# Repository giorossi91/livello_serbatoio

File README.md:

# Tank level monitor

## Scope
This project realizes a simple device to monitor the water level in a tank.

## Architecture
The monitor is realized with an ATMEGA328P microcontroller to run the SW produced with Arduino IDE environment, an ultrasonic sensor to measure the level of the water and an LCD 16x2 characters to show the liters amount associated to the percentage of filling.

## Sofware
The SW has been developed with Arduino IDE and tested with CppUnit and a Qt GUI used to simulate the external environment.

## Phases of the project
### Phase 1 (Prototype)
The project was realized on a prototype board using the schematic in `schemi\schema_scheda.pdf`. The microcontroller was hosted in an Arduino UNO rev3 board.
The schematic was realized with Fritzing. The enclosure was hand-made and adapted from an existing one.

### Phase 2 (Finished)
The entire schematic was re-designed with Kicad and a PCB has been designed and produced. The enclosure has been designed with Freecad and 3D printed.

## Project Website
Go to [project website](https://giorossi91.github.io/livello_serbatoio)

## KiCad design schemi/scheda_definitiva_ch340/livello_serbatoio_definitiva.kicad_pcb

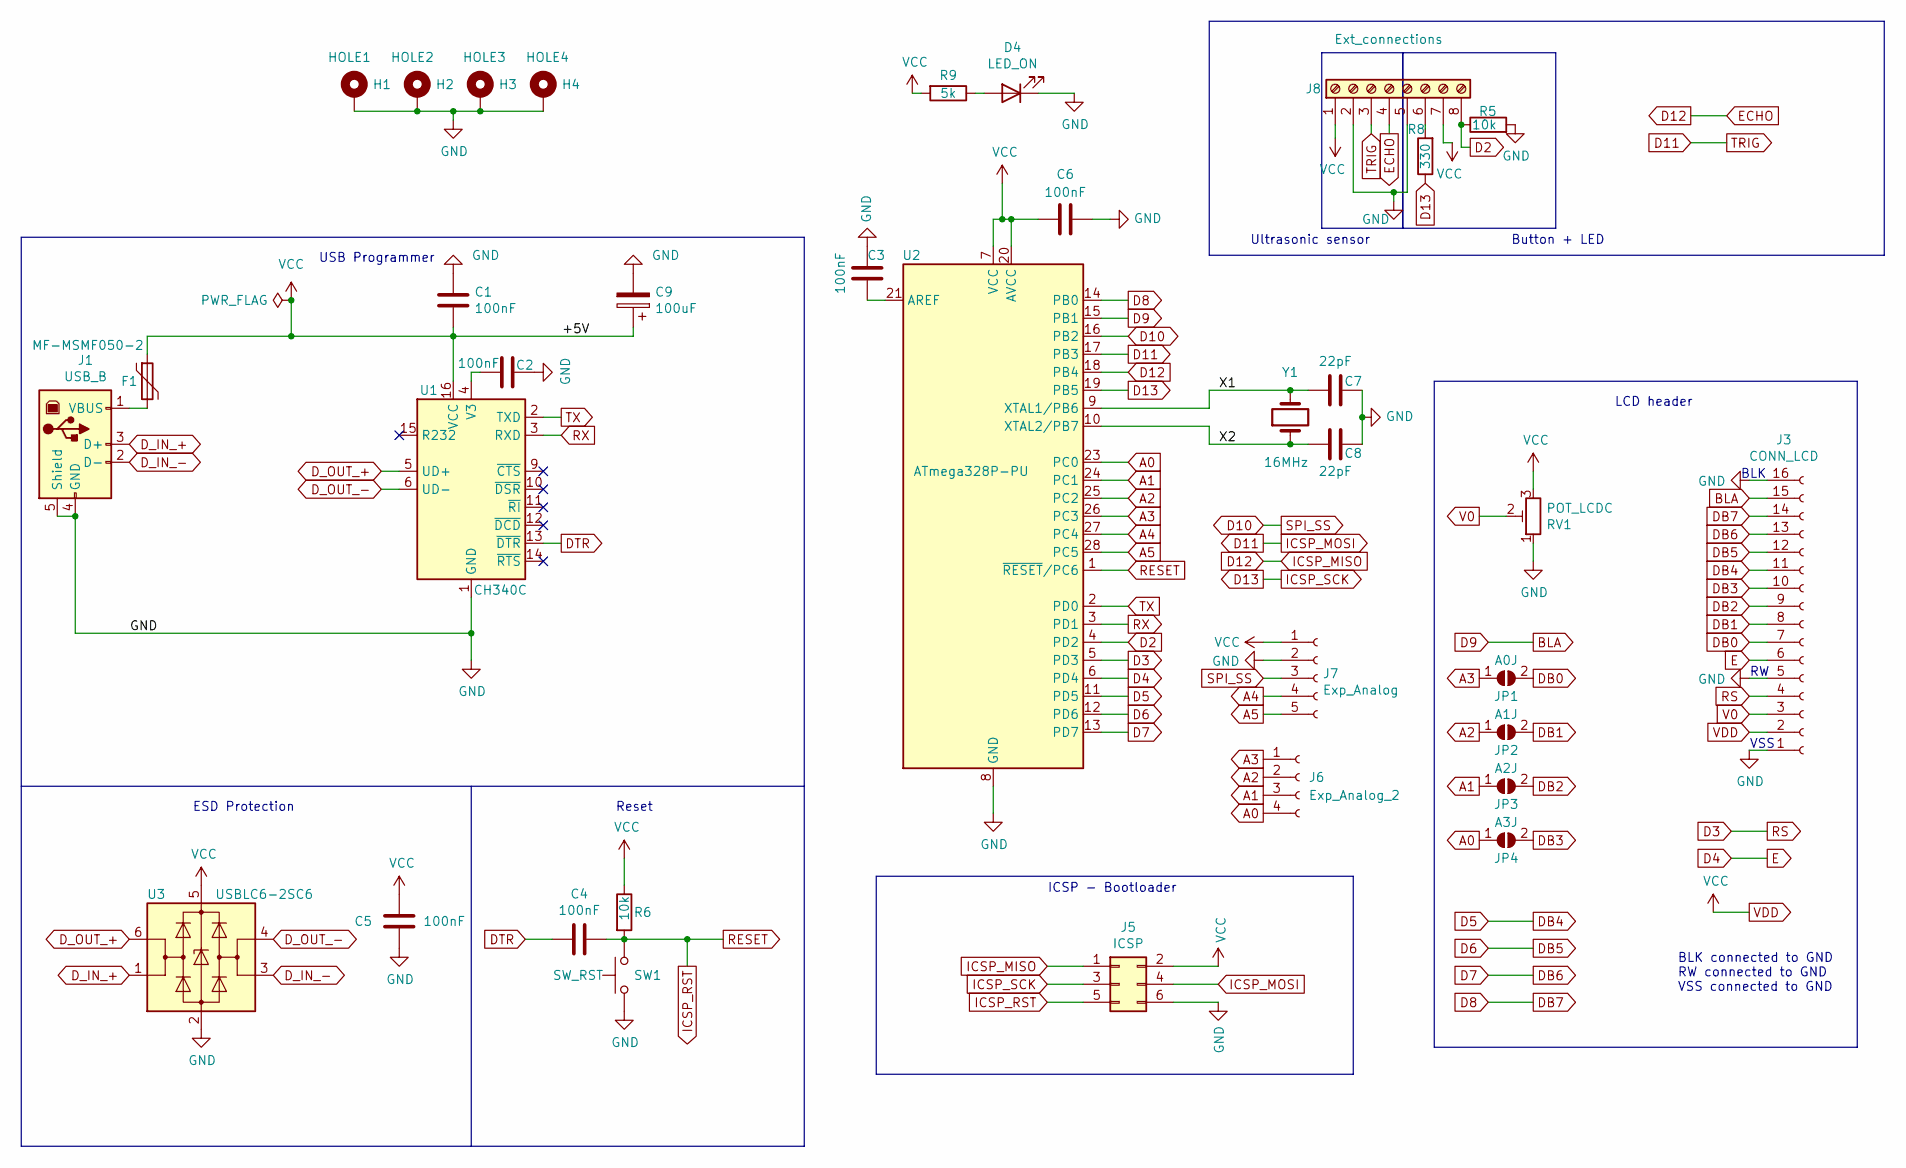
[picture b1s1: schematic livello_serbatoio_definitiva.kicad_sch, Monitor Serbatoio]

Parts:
C1, C2, C3, C4, C5, C6: 100nF; C_Disc_D5.0mm_W2.5mm_P2.50mm
C7, C8: 22pF; C_Disc_D5.0mm_W2.5mm_P2.50mm
C9: 100uF; CP_Radial_D5.0mm_P2.00mm
D4: LED_ON; LED_D5.0mm
F1: MF-MSMF050-2; MF-MSMF_1812_4532Metric_Pad1.30x3.40mm_HandSolder
H1: HOLE1; MountingHole_3mm_Pad_Via
H2: HOLE2; MountingHole_3mm_Pad_Via
H3: HOLE3; MountingHole_3mm_Pad_Via
H4: HOLE4; MountingHole_3mm_Pad_Via
J1: USB_B; USB_B_OST_USB-B1HSxx_Horizontal
J3: CONN_LCD; PinSocket_1x16_P2.54mm_Vertical
J5: ICSP; PinHeader_2x03_P2.54mm_Vertical
J6: Exp_Analog_2; PinSocket_1x04_P2.54mm_Vertical
J7: Exp_Analog; PinSocket_1x05_P2.54mm_Vertical
J8: Ext_connections; TerminalBlock_RND_205-00051_1x08_P5.00mm_Horizontal
JP1: A0J; SolderJumper-2_P1.3mm_Open_Pad1.0x1.5mm
JP2: A1J; SolderJumper-2_P1.3mm_Open_Pad1.0x1.5mm
JP3: A2J; SolderJumper-2_P1.3mm_Open_Pad1.0x1.5mm
JP4: A3J; SolderJumper-2_P1.3mm_Open_Pad1.0x1.5mm
R5, R6: 10k; R_Axial_DIN0309_L9.0mm_D3.2mm_P12.70mm_Horizontal
R8: 330; R_Axial_DIN0309_L9.0mm_D3.2mm_P12.70mm_Horizontal
R9: 5k; R_Axial_DIN0309_L9.0mm_D3.2mm_P12.70mm_Horizontal
RV1: POT_LCDC; Trimmer_ACP_470
SW1: SW_RST; SW_PUSH_6mm_H5mm
U1: CH340C; SOIC-16_3.9x9.9mm_P1.27mm
U2: ATmega328P-PU; DIP-28_W7.62mm
U3: USBLC6-2SC6; SOT-23-6_Handsoldering
Y1: 16MHz; Crystal_TH_AS16_5mm

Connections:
/X1: C7.2, U2.9 (XTAL1/PB6), Y1.2
/X2: C8.2, U2.10 (XTAL2/PB7), Y1.1
A0: J6.4, JP4.1 (A), U2.23 (PC0)
A1: J6.3, JP3.1 (A), U2.24 (PC1)
A2: J6.2, JP2.1 (A), U2.25 (PC2)
A3: J6.1, JP1.1 (A), U2.26 (PC3)
A4: J7.4, U2.27 (PC4)
A5: J7.5, U2.28 (PC5)
BLA: J3.15, U2.15 (PB1)
D2: J8.8, R5.1, U2.4 (PD2)
D3: J3.4, U2.5 (PD3)
D4: J3.6, U2.6 (PD4)
D5: J3.11, U2.11 (PD5)
D6: J3.12, U2.12 (PD6)
D7: J3.13, U2.13 (PD7)
D8: J3.14, U2.14 (PB0)
D10: J7.3, U2.16 (PB2)
D11: J5.4, J8.3, U2.17 (PB3)
D12: J5.1, J8.4, U2.18 (PB4)
D13: J5.3, R8.1, U2.19 (PB5)
DB0: J3.7, JP1.2 (B)
DB1: J3.8, JP2.2 (B)
DB2: J3.9, JP3.2 (B)
DB3: J3.10, JP4.2 (B)
DTR: C4.2, U1.13 (~DTR)
D_IN_+: J1.3 (D+), U3.1 (I/O1)
D_IN_-: J1.2 (D-), U3.3 (I/O2)
D_OUT_+: U1.5 (UD+), U3.6 (I/O1)
D_OUT_-: U1.6 (UD-), U3.4 (I/O2)
GND: C1.1, C2.2, C3.2, C5.1, C6.2, C7.1, C8.1, C9.2, D4.1 (K), H1.1, H2.1, H3.1, H4.1, J1.4 (GND), J1.5 (Shield), J3.1, J3.5, J3.16, J5.6, J7.2, J8.2, J8.5, R5.2, RV1.1, SW1.1, U1.1 (GND), U2.8 (GND), U2.22 (GND), U3.2 (GND)
ICSP_RST: C4.1, J5.5, R6.2, SW1.2, U2.1 (~RESET/PC6)
unnamed: D4.2 (A), R9.1
unnamed: F1.2, J1.1 (VBUS)
unnamed: J8.6, R8.2
unnamed: C2.1, U1.4 (V3)
unnamed: C3.1, U2.21 (AREF)
RX: U1.3 (RXD), U2.3 (PD1)
TX: U1.2 (TXD), U2.2 (PD0)
V0: J3.3, RV1.2
VDD: C1.2, C5.2, C6.1, C9.1, F1.1, J3.2, J5.2, J7.1, J8.1, J8.7, R6.1, R9.2, RV1.3, U1.16 (VCC), U2.7 (VCC), U2.20 (AVCC), U3.5 (VBUS)

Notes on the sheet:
ESD Protection
BLK
Reset
USB Programmer
Ultrasonic sensor
BLK connected to GND RW connected to GND VSS connected to GND
VSS
Button + LED
ICSP - Bootloader
LCD header

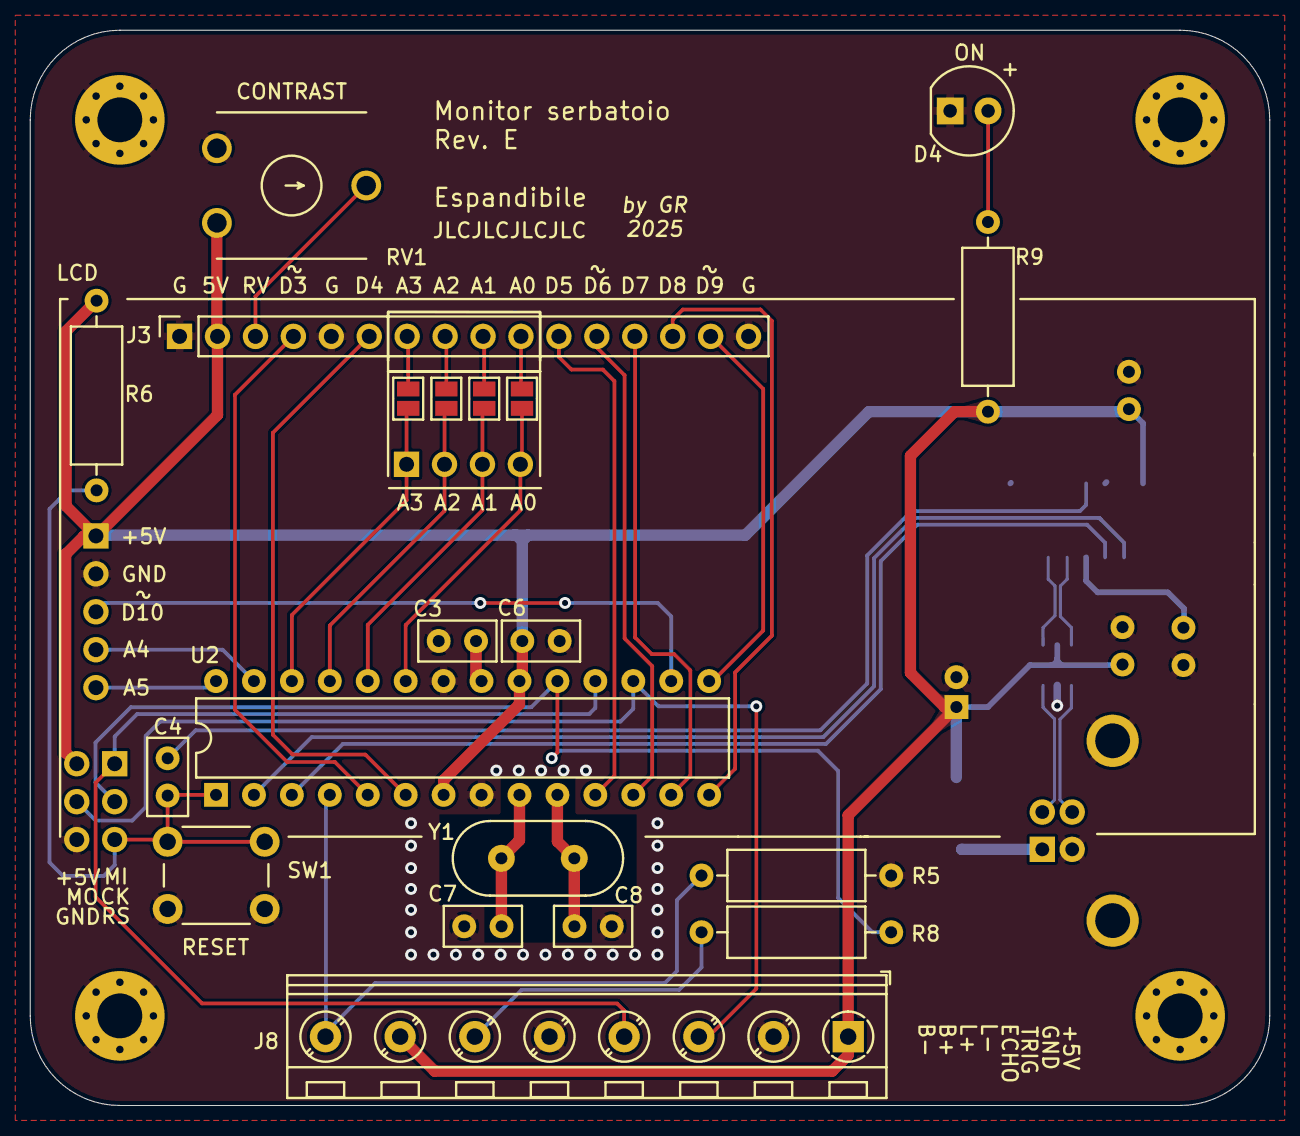
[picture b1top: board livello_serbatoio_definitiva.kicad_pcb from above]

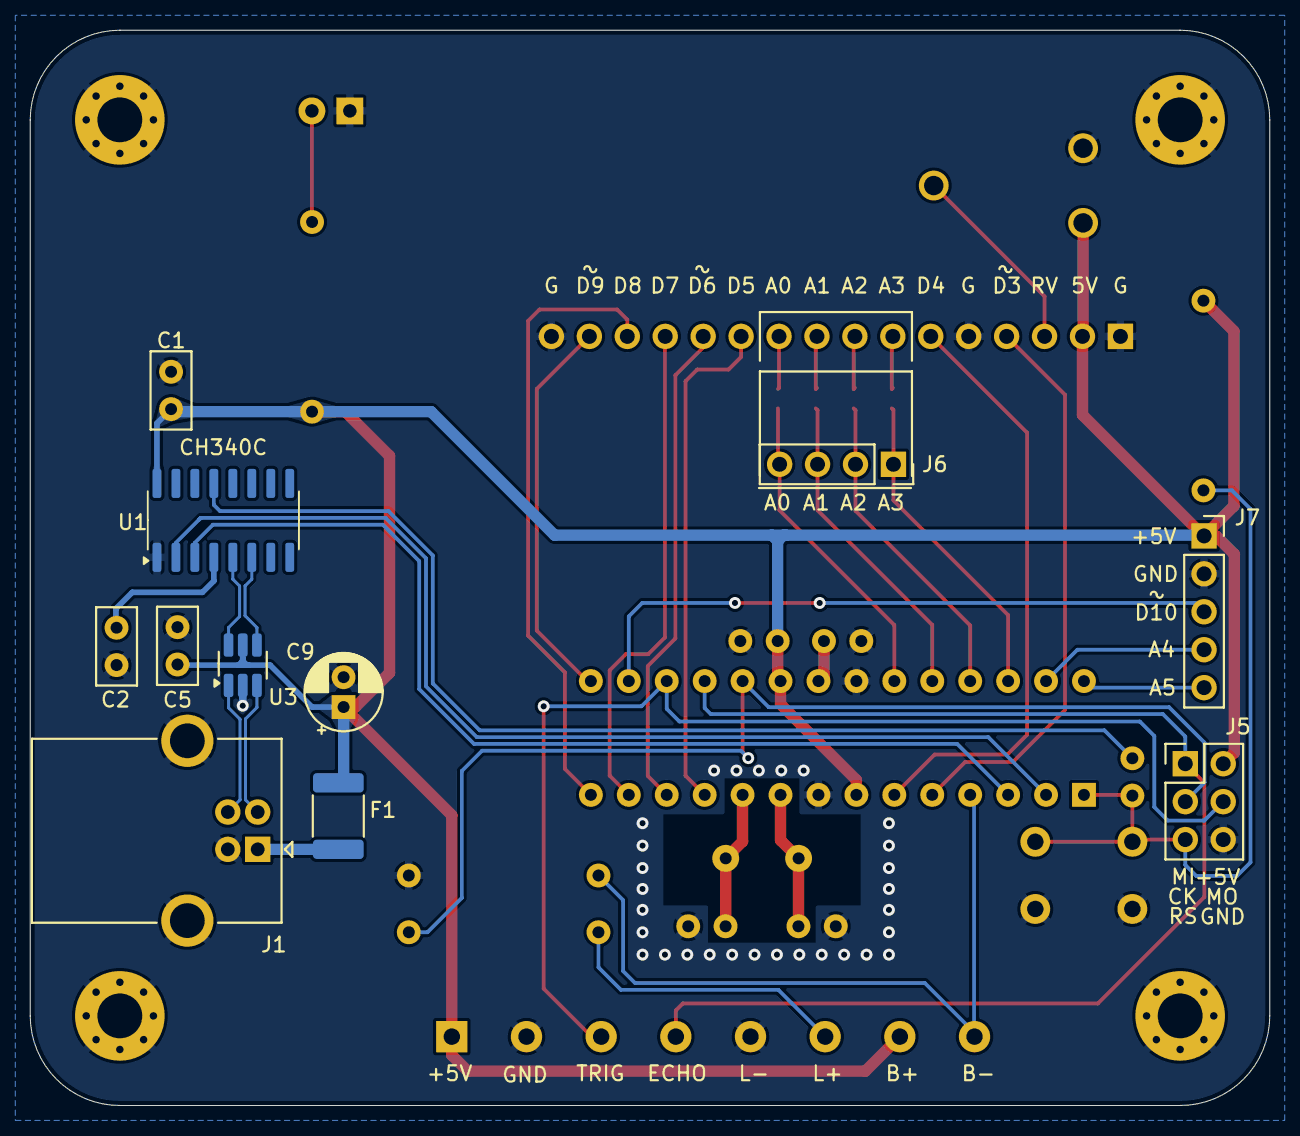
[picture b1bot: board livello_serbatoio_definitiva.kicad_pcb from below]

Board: 2 copper layers, 83.0 x 72.0 mm, 35 parts (11 on the bottom side), 40 nets.

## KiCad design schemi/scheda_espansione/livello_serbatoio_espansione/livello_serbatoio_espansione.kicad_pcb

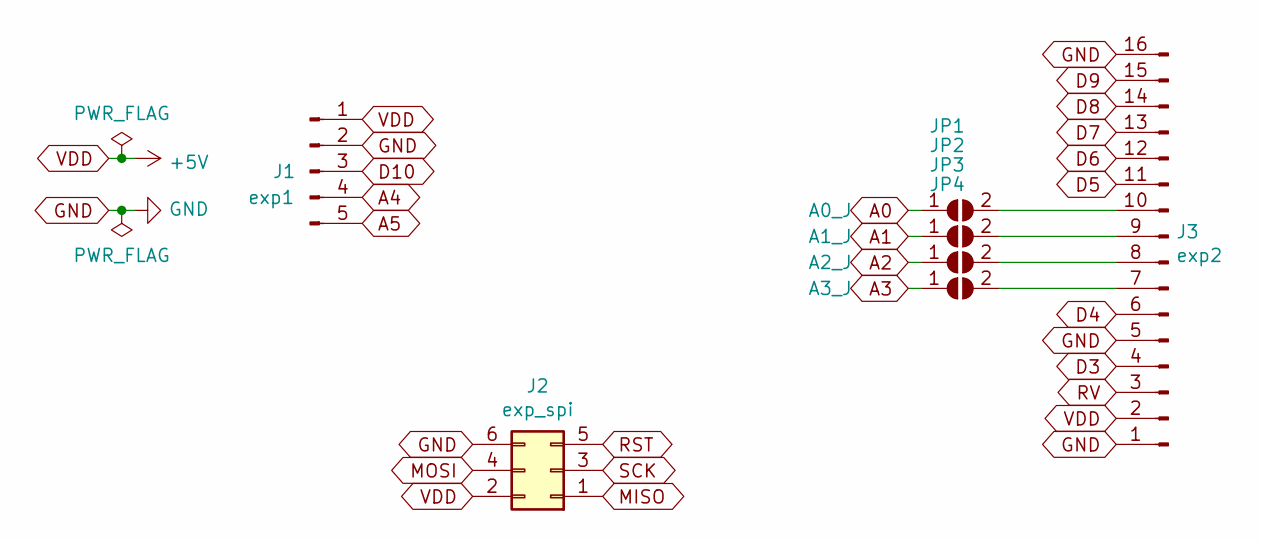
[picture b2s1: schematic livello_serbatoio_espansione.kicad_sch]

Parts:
J1: exp1; PinHeader_1x05_P2.54mm_Vertical
J2: exp_spi; PinSocket_2x03_P2.54mm_Vertical
J3: exp2; PinHeader_1x16_P2.54mm_Vertical
JP1: A0_J; SolderJumper-2_P1.3mm_Open_Pad1.0x1.5mm
JP2: A1_J; SolderJumper-2_P1.3mm_Open_Pad1.0x1.5mm
JP3: A2_J; SolderJumper-2_P1.3mm_Open_Pad1.0x1.5mm
JP4: A3_J; SolderJumper-2_P1.3mm_Open_Pad1.0x1.5mm

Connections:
A0: JP1.1 (A); also elsewhere on the board
A1: JP2.1 (A); also elsewhere on the board
A2: JP3.1 (A); also elsewhere on the board
A3: JP4.1 (A); also elsewhere on the board
A4: J1.4
A5: J1.5
D3: J3.4
D4: J3.6
D5: J3.11
D6: J3.12
D7: J3.13
D8: J3.14
D9: J3.15
D10: J1.3
GND: J1.2, J2.6, J3.1, J3.5, J3.16
MISO: J2.1
MOSI: J2.4
unnamed: J3.7, JP4.2 (B)
unnamed: J3.8, JP3.2 (B)
unnamed: J3.9, JP2.2 (B)
unnamed: J3.10, JP1.2 (B)
RST: J2.5
RV: J3.3
SCK: J2.3
VDD: J1.1, J2.2, J3.2

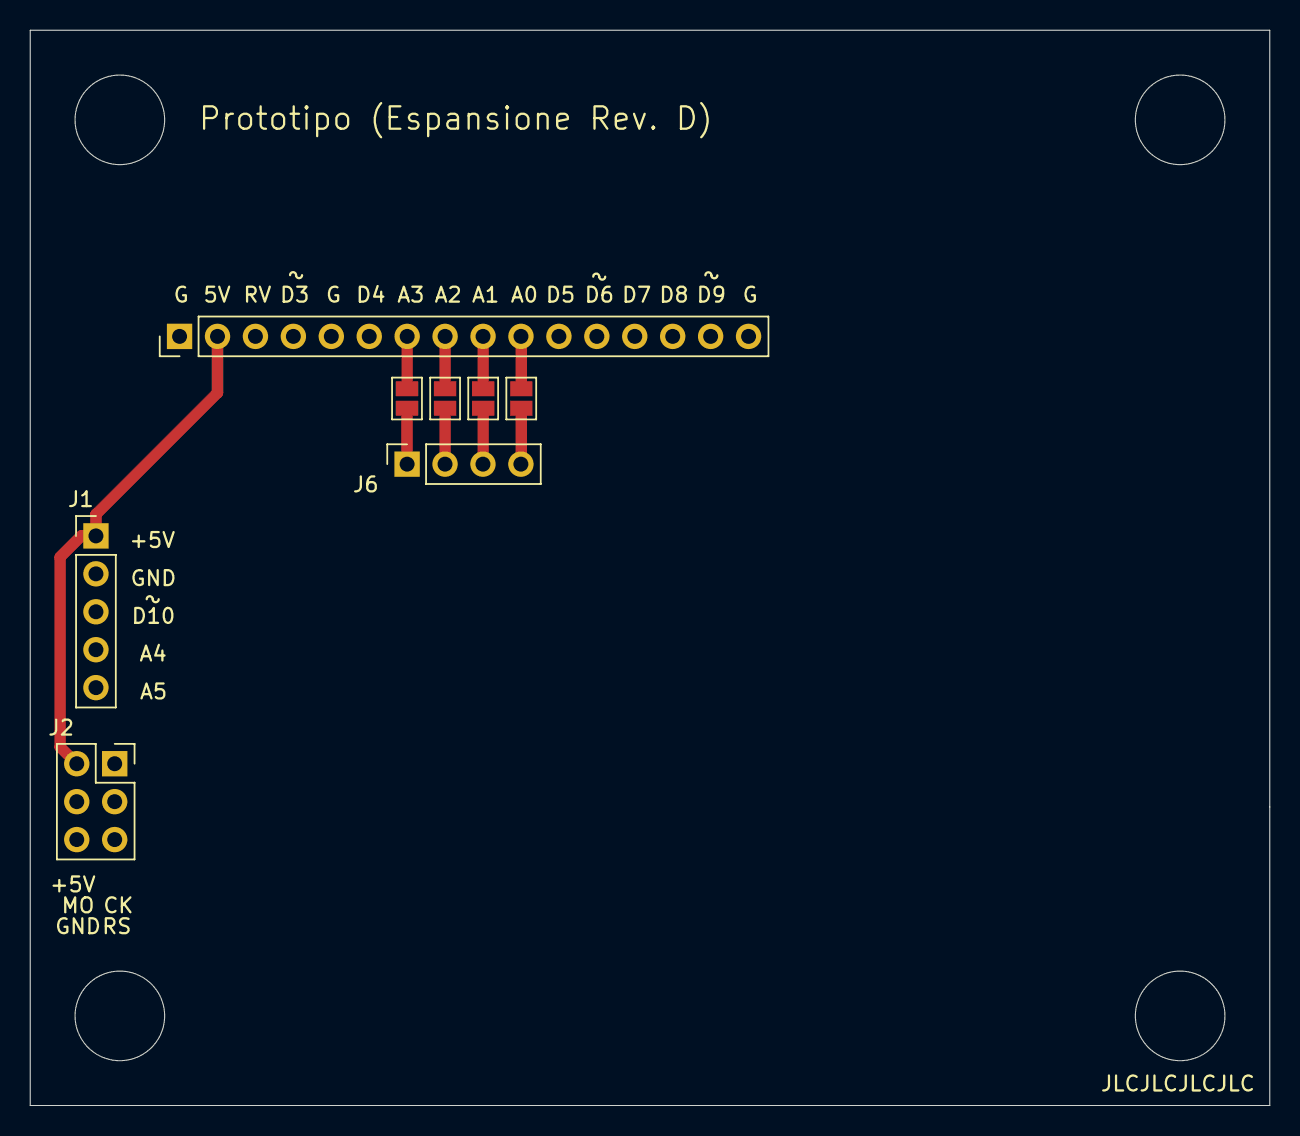
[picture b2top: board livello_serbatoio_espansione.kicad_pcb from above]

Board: 2 copper layers, 83.0 x 72.0 mm, 8 parts (0 on the bottom side), 10 nets.

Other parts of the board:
J6: Exp_Analog_2; PinSocket_1x04_P2.54mm_Vertical

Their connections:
A0: J6.4; also elsewhere on the board
A1: J6.3; also elsewhere on the board
A2: J6.2; also elsewhere on the board
A3: J6.1; also elsewhere on the board

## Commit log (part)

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2017-08-22 aggiunto script calcolo livello serbatoio
2017-08-29 aggiornato sketch - aggiunta distanza sensore da livello massimo - migliorata gestione timer lcd on e intervallo di misura - tradotti nomi variabili in inglese - calcolo capienza serbatoio corretto -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
2017-09-02 modifica layout lcd - modalità release + aggiunto schema pcb (bozza da completare)
2017-09-03 aggiornamento lcd
2017-09-09 aggiornato pinout
2017-12-26 fix misura litri
2017-12-26 implementato smoothing letture distanza
2017-12-26 introdotto median filter per i dati della distanza e aggiornato sketch
2018-01-27 aggiunto messaggio di boot + pdf schema
2018-01-27 modificata finestra lettura MedianFilter
2018-08-07 Taratura sensore + bug fixing - corretto rendering litri - corretti commenti - aumentato tempo campionamento - introdotto arrotondamento distanza a intero più vicino (migliore stabilità misure, preci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
2018-08-10 corretto controllo overflow distanza + introdotto check riempimento serbatoio con indicatore sul display (freccia custom)
2018-08-13 rimosso controllo riempimento (non utile) + ripristinato sleep a 1.5s per led
2018-08-18 rimosso PULL_UP a input lcd + cambiato carattere barra progresso
2018-11-10 introdotto controllo errore per funzione pulseIn
2018-11-10 aggiunto schematico scheda d'interfaccia
2018-12-23 Aggiunta compensazione errore del nuovo sensore
2019-08-08 Inserita doppia configurazione per vecchio sensore e nuovo waterproof - Calibrazione distanza
2019-08-11 Aggiornato sketch - Refactory codice - Risoluzione bug (refresh lcd, boot lungo, size variabili) - Aggiunta documentazione - Uniti file in un unico sketch
2019-08-16 bug fix + funzione autotest
2019-08-17 aggiunto gitignore
2019-08-17 Aggiunta classe per controllo statistiche [in implementazione]
2019-08-17 aggiunto print versione
2019-08-17 classe calcolo statistiche consumo
2019-08-20 aggiunta print stats su LCD (da testare)
2019-08-21 Completato display su LCD delle statistiche
2019-08-21 [da testare] fix statistiche consumo
2019-08-22 [da testare] fix soglia di riempimento in updateConsumption
2020-06-13 Riorganizzazione repository. Rimossa cartella MediaFilter in seguito ad integrazione in un file unico. Aggiunta cartella schemi che include tutti gli schematici realizzati in formato fritzing e pdf.
2020-06-13 Aggiunta base per unit testing con cppunit
2020-06-20 creata test harness per LCD e Serial e stub
2020-06-21 Aggiunto progetto Eclipse per supporto coverage
2020-06-28 Unit test e coverage - Aggiunti unit test per compute_liters, compute_percentage, turn_on_lcd_light, turn_off_lcd_light, measure_level, control_led, sanitize_data - Aggiunto rapporto coverage creato 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
2020-06-29 aggiunti nuovi test per LCD - vari fix sullo sketch - aggiornata coverage - aggiornato makefile
2020-08-02 nuovi test + schematico - bozza schematico per scheda definitiva (realizzato con KiCAD) - implementati nuovi test per MedianFilter - bozza test per StatisticheConsumo - piccole revisioni a sketch (ri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
2020-08-03 aggiornati unit test - nuovi test per StatisticheConsumo - fix su updateTime in StatisticheConsumo
2020-08-05 nuovi unit test + simulatore - aggiunti test per StatisticheConsumo - aggiunto simulatore Qt per testing e debugging senza scheda
2020-08-08 aggiunto grafico D/IO a simulatore
2020-08-09 migliorata gestione serie ed introdotto monitoraggio segnali
2020-08-13 nuovi test per funzione loop + modifiche a sketch - inizializzazione oggetti con metodo begin e initialize - fix stampa errore e recovery in seguito ad errore sensore
2020-08-14 test unitario loop completo
2020-08-17 fix a schema definitivo e assegnate footprint
2020-08-18 caricamento prima bozza PCB + piccoli fix a footprint
2020-08-19 modifiche a scheda definitiva - aggiunto footprint LCD di riferimento - modificato schematico per aggiungere connettore ICSP e fori di montaggio a massa - ricollocati connettori - da rivedere colloca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
2020-08-20 spostato UC in PCB per conflitto con LCD + aggiunto modello 3d Cristallo
2020-08-21 riposizionati connettori + auto-routing eseguito con freerouting
2020-08-22 Revisioni a PCB - aggiunta versione a PCB - revisione piste - generato piano di massa - aggiunto gerber
2020-08-22 prima bozza box da completare
2020-08-29 modello 3d completo - lcd - box
2020-10-11 fix alimentazioni + introduzione coppia differenziale per USB - da rivedere piste USB per match lunghezza/skew/impedenza
2020-10-18 spostati componenti e fatto nuovo sbroglio
2020-10-24 rivisto routing di alcune piste
2020-10-24 modifica traccia usb + rigenerato gerber
2020-10-25 modificato gerber / disegno 3D box / nuove immagini render aggiunte
2020-11-07 nuovo routing + BOM + aggiornamento lista componenti
2020-11-08 fix a scheda - corrette footprint (adeguate a componenti in possesso) - nuovo routing e layout scheda - aggiunto logo - aggiornato gerber
2020-11-14 aggiunta protezione ESD - nuovo routing usb - nuove immagini pcb
2020-11-15 allineamento modello 3d + fix minori pcb - aggiornato modello box - aggiunto logo a box - nuovi modelli 3d fusibile e trimmer - aggiornato sch per fusibile - aggiornato pcb - nuove immagini + doc pro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
2020-11-15 aggiornato gerber PCB
2020-11-21 revisione routing pcb
2020-11-21 esportati pin per espandibilità
2020-11-22 revisioni minime a pcb
2020-11-23 fix footprint trimmer - aggiornato pcb
2020-11-28 aggiornamento PCB - ridefinite filled zone - stondati bordi - cambiato connettore per espansione - rimosse via per GND
2020-11-29 piccole revisioni PCB - spostate alcune piste per maggiore copertura filled zone - rivisti alcuni parametri per manufacturing (dimensione scritte, S/N) - rimosse alcune vie e piste per piano GND inut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
2020-11-30 revisionata connessione DTR logica reset - revisionato wiring DTR - aggiornato PCB - ricreato gerber
2020-12-01 revisione piste circuito reset - spostata pista DTR - spostato pulsante - aggiornato piano di massa - rimossa una via su DTR
2020-12-04 aggiunto ulteriore connettore per espansioni - riviste piste - rivisti piani di massa
2020-12-05 revisione pcb - fix misure lcd - spostate alcune piste
2020-12-06 aumentate dimensioni track +5V - rivisto layout di alcune piste - aggiunti commenti su layout
2020-12-08 spostato LCD e rifatto modello box - LCD centrato su LCD - revisione layout - nuovo modello box (box + coperchio + pulsante + assembly scheda e lcd) - aggiornate immagini prototipo - creati file stl 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
2020-12-12 creato modello 3d box ad incastro
2020-12-20 fix mesh box
2020-12-20 aggiunta tolleranza ad incastro
2020-12-22 piccoli fix a PCB
2020-12-24 Creata prima bozza README
2020-12-27 aggiunte piazzole CTS/RTS + aggiunte etichette a pin digitali - rivisto gerber - rivista footprint oscillatore
2020-12-28 fix serigrafie PCB - generato gerber - caricamento test seriale
2020-12-30 caricamento prototipo espansione - schema elettrico + pcb - assemblaggio 3d con scheda di espansione
2021-02-13 modifica per seriale - aggiunto elettrolitico per alimentazione - fix test seriale
2021-03-06 aggiunta ferrite a scheda rev. B
2021-05-23 disconnesso pin reset di ft232
2021-06-27 Rimosso interrupt a pressione pulsante ed introdotto tempo di pressione corto - Aggiornato simulatore - Aggiornati unit test
2021-08-06 modificata gestione pulsante e aggiunta modalità maintenance
2021-08-07 Refactory - funzione menu con un tasto - traduzione commenti in inglese - rinomina variabili per uniformità
2021-08-08 Refactory - completata documentazione codice - aggiunta opzione menu per visualizzare i parametri dei serbatoi
2021-08-09 fix warning compilatore
2021-08-10 piccoli fix (commenti, formattazione)
2021-08-10 refactory ambiente di test
2021-08-10 rimossi file html non necessari / modificati progetti Qt test
2021-08-11 caricamento configurazioni progetto Qt
2021-08-12 fix su visualizzazione errore + unit test loop e bottone
2021-08-12 fix visualizzazione 'menu' su display
2021-08-12 fix flickering LCD in visualizzazione menu
2021-08-13 fix lcd backlight in modalità maintenance
2021-08-13 fix visualizzazione uscita menu
2021-08-13 [WIP] classe LcdHelper
2021-08-14 fix visualizzazione update_lcd
2021-08-17 Fix + doc - [fix] backlight non funzionante in Manutenzione - [fix] lcd non funzionante con LcdHelper - [fix] doc doxygen
2021-08-20 aggiunta documentazione e irrobustimento codice
2021-08-21 generazione automatica doc doxygen
2021-08-21 modificato path deploy doc
2021-08-21 deploy: 463d8ce6dc005a2671d0c78f108b0ae5952e7eed
2021-08-21 modificato input Doxyfile
2021-08-21 deploy: e4e8b633e6bd199e500c4c8521c170289cdc8f01
2021-08-21 modificato path output
2021-08-21 deploy: 650f3bfb92a4f9c400058111fde89389696d4a15
2021-08-21 fix publish_dir
2021-08-21 deploy: ee4b6ec08cbe2fd2f6fc105f4916d9d3cda1a947
2021-08-21 cambiato branch trigger per generazione doc
2021-08-23 test aggiunta html
2021-08-23 test html
2021-08-23 aggiunta cartella docs
2021-08-23 deploy: e5e390484499ddf692092b3da53c0939733db460
2021-08-23 Set theme jekyll-theme-slate
2021-08-23 test docs folder
2021-08-23 test deploy doxy
2021-08-23 test fix doxy path
2021-08-23 deploy: 4e36ef79c9283fe8fdf9c03f315c7e99b322637e
2021-08-23 test keep_file 1
2021-08-23 test keep_file 2
2021-08-23 deploy: 439377a263196b7e16ae1fd7de678b631a6828a5
2021-08-23 test keep_file 3
2021-08-23 clean gh-pages
2021-08-23 test keep_file 4
2021-08-23 deploy: bd374bbc9395080fb0511899583994d255c29fbb
2021-08-23 test jekyll 1
2021-08-23 test dir 1
2021-08-23 test dir 2
2021-08-23 test dir 3
2021-08-23 Rename test.html to schematics.html
2021-08-24 aggiornamento README con link a sito progetto
2021-08-25 adattamento test unitari a lcdhelper
2021-08-25 deploy: f274c2b1eefa49c81c8a804e66053792a78dfbf0
2023-08-03 schema serbatoio
2023-08-11 modifiche scheda definitiva (rev. C)
2023-08-11 v0.9: fix dimensioni serbatoio
2023-08-14 v0.11 - introdotto controllo su misure sensore (livello crescente, decrescente, stazionario) - rilevamento valori rumorosi per detezione fault sensore
2024-04-26 scheda rev.D - rimosse resistenze RX/TX seriale - aggiustamento label
2024-05-05 scheda rev. D - applicate revisioni - allineati vincoli a capability jlc - adattata scheda prototipo
2025-08-16 mod workflow per eseguire pipeline al push su master e dev
2025-08-16 fix lettura stato riempimento serbatoio
2025-08-16 deploy: ce42753aa501c01fb8ee47532ae4bf9fca2f008e
2025-08-17 fix misura tendenza - aggiornato framework per print float su lcd - abbassata freq letture HF - cambiata print debug
2025-08-17 deploy: 2b1b62b37dd19d5e1a0b6ffbfb8f4ff6e14be678
2025-08-21 revisioni minori - nomi variabili - formattazione - documentazione
2025-08-21 deploy: 842a7b15bb9bbfd371423021a89e60e24eae49bf
2025-08-21 aggiornato doxyfile a versione più recente ed aggiornato gh workflow
2025-08-21 deploy: 2c79b735983c54c0b10b33baa45fe3b18acaf1b9
2025-08-21 aggiornati unit test
2025-08-22 corretto schema (placing fuse e condensatori filtro)
2025-08-22 deploy: c8b62f635f4a265e67522386675d38e648a4d7e8
2025-08-23 revisioni pcb (rimosse violazione jlcpcb) aggiunti stl per case e coperchio da fusion360
2025-08-23 deploy: ab3a95fcb5e9fa9c54aa3631fd215543845cd80f
2025-08-25 aggiunta nuova revisione scheda con ch340 al posto di ft232rl
2025-08-25 deploy: fee9864e8c49d120c1be85e178f793bb94a71533
2025-10-26 Update schematics.html to use iframes for viewing
    Replaced Altium ECAD viewer with iframes for embedded views.
2025-10-26 Fix image syntax in index.md
2025-11-16 aggiornata data su coperchio box
2025-11-16 deploy: e32ce0e86bb264b37c01a6e8af969bf75a8fc0a8
2025-11-16 aggiunte tolleranze ai modelli 3D
2025-11-16 deploy: bf2ef3477305b5998b735db321682a7427458778
2026-06-28 fix qt projects - auto deploy - uso diretto di livello_serbatoio.ino
